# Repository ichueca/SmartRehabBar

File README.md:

# SmartRehabBar

**SmartRehabBar** es un proyecto centrado en el **desarrollo de un sistema inteligente que se integra en barras de rehabilitación**, permitiendo medir de forma objetiva la fuerza de apoyo ejercida por pacientes durante ejercicios de recuperación funcional.

El sistema utiliza **células de carga** para registrar la carga aplicada, enviando los datos en tiempo real a una plataforma web para su visualización. Esto permite a los profesionales sanitarios realizar un seguimiento cuantitativo de la evolución del paciente.

Además, el proyecto está diseñado con un enfoque **educativo y modular**, facilitando su uso en Formación Profesional y permitiendo futuras ampliaciones como análisis avanzado e integración de inteligencia artificial.

---

## 🎯 Objetivos del proyecto

* Medir de forma objetiva la **fuerza de apoyo** durante ejercicios de rehabilitación.
* Registrar el **tiempo de carga** y detectar descompensaciones.
* Facilitar datos cuantitativos al fisioterapeuta.
* Desarrollar un sistema **replicable, modular y de bajo coste**.
* Servir como base para futuras ampliaciones (doble apoyo, IA, análisis avanzado).

---

## 🧩 Arquitectura general del sistema

El sistema electrónico se compone de los siguientes bloques:

1. Sensórica de fuerza mediante células de carga.
2. Amplificación y conversión ADC con HX711.
3. Microcontrolador ESP32 para procesado y comunicaciones.
4. Sistema de alimentación autónomo con batería Li-Ion.
5. Comunicación WiFi con servidor remoto para visualización de datos.

---

## 🧪 Material electrónico utilizado

### Sensores

* **Células de carga resistivas** (galgas extensométricas).
* Configuración en puente de Wheatstone para mayor estabilidad.

### Conversión y amplificación

* **HX711**

  * ADC de 24 bits específico para células de carga.
  * Alta precisión para señales de baja variación.

### Microcontrolador

* **ESP32 / ESP32-C3 SuperMini**

  * Lectura del HX711.
  * Procesado de datos.
  * Comunicación WiFi.
  * Envío de datos a backend REST.

### Alimentación

* **Batería Li-Ion 18650** (3.0–4.2 V).
* **MCP73871**

  * Gestión de carga.
  * Power-path (uso y carga simultánea).
* **Convertidor Buck-Boost (TPS63020)**

  * Generación de tensión estable para el sistema (3.3 V).
* **Divisor resistivo**

  * Medición del voltaje de batería mediante ADC.

---

## 🧠 Firmware

En este repositorio se incluyen varias versiones del firmware:

### 🔹 PesajeV1

Primera versión funcional del sistema.

**Características:**

* Medición de fuerza en **un único punto de apoyo**.
* Lectura mediante HX711.
* Envío de datos de peso.
* No incluye medición de batería.
* Base para validación inicial.

---

### 🔹 PesajeV2

Versión mejorada del sistema.

**Novedades:**

* ✅ Medición de **nivel de batería en porcentaje**.
* ✅ Lectura de batería mediante ADC + divisor resistivo.
* ✅ Calibración del ADC para mayor precisión.
* ✅ Mejora en estabilidad de lectura.

---

### 🔹 PesajeV3

Versión actual del sistema.

**Novedades principales:**

* ✅ Medición de **doble apoyo (pie izquierdo y derecho)**.
* ✅ Uso de **dos módulos HX711** (uno por cada plataforma).
* ✅ Migración a **ESP32-C3 SuperMini** (reducción de tamaño y consumo).
* ✅ Lectura simultánea de ambos sensores.
* ✅ Envío independiente de datos de cada pie al backend.
* ✅ Mejora en la arquitectura del firmware (estructura modular).

Esta versión permite analizar **asimetrías de carga entre ambos pies**, siendo mucho más útil en entornos reales de rehabilitación.

---

### 🔮 Versiones futuras

* Mejora de filtrado y tratamiento de señal.
* Detección de eventos (apoyo, descarga, equilibrio).
* Optimización de consumo energético.
* Integración de análisis avanzado e IA.
* Visualización avanzada de métricas (balance, evolución, tendencias).

---

## 🔌 Hardware (KiCad)

El repositorio incluye el diseño electrónico completo desarrollado en **KiCad**:

### Contenido:

* 📄 Esquema eléctrico
* 🧩 Diseño de PCB
* 📦 Archivos listos para fabricación

### Versiones:

* Hardware compatible con **PesajeV1**
* Hardware actualizado para **PesajeV2 (medición de batería)**
* 🆕 Hardware **SmartRehab V3**

  * Soporte para **doble HX711**
  * Integración con **ESP32-C3 SuperMini**
  * Optimización del sistema de alimentación
  * Diseño compacto orientado a integración en plataforma

---

## 🔁 Pasos para la replicación

1. Definición del caso de uso.
2. Selección de sensores de fuerza.
3. Integración con HX711.
4. Implementación con ESP32.
5. Diseño del sistema de alimentación.
6. Desarrollo del firmware.
7. Validación con cargas reales.

---

## ⚠️ Consideraciones importantes

* Este sistema es una **herramienta de apoyo**, no un dispositivo médico certificado.
* La fijación mecánica de las células de carga es crítica.
* El sistema está diseñado para ser **modular y ampliable**.
* La medición de batería requiere calibración del ADC.
* Las mediciones de peso requieren **calibración (tara + escala)** tras cambios mecánicos.

---

## 📁 Estructura del repositorio

* `/firmware`

  * `PesajeV1`
  * `PesajeV2`
  * `PesajeV3` 🆕
* `/hardware`

  * `PCB_SmartRehab_V1`
  * `PCB_SmartRehab_V2`
  * `PCB_SmartRehab_V3` 🆕
* `/docs` → Documentación adicional

---

## 📱 Repositorio de la App

Frontend y visualización de datos:
https://github.com/ichueca/SmartRehabBar-App

---

## 👥 Autores

* Jonathan Arizala – https://lasalleberrozpe.eus
* Ainhoa Domínguez – https://nazaret.eus/
* Iñigo Chueca – https://www.zabalburu.org

Proyecto subvencionado por la Viceconsejería de Formación Profesional del Gobierno Vasco a través de https://tknika.eus/

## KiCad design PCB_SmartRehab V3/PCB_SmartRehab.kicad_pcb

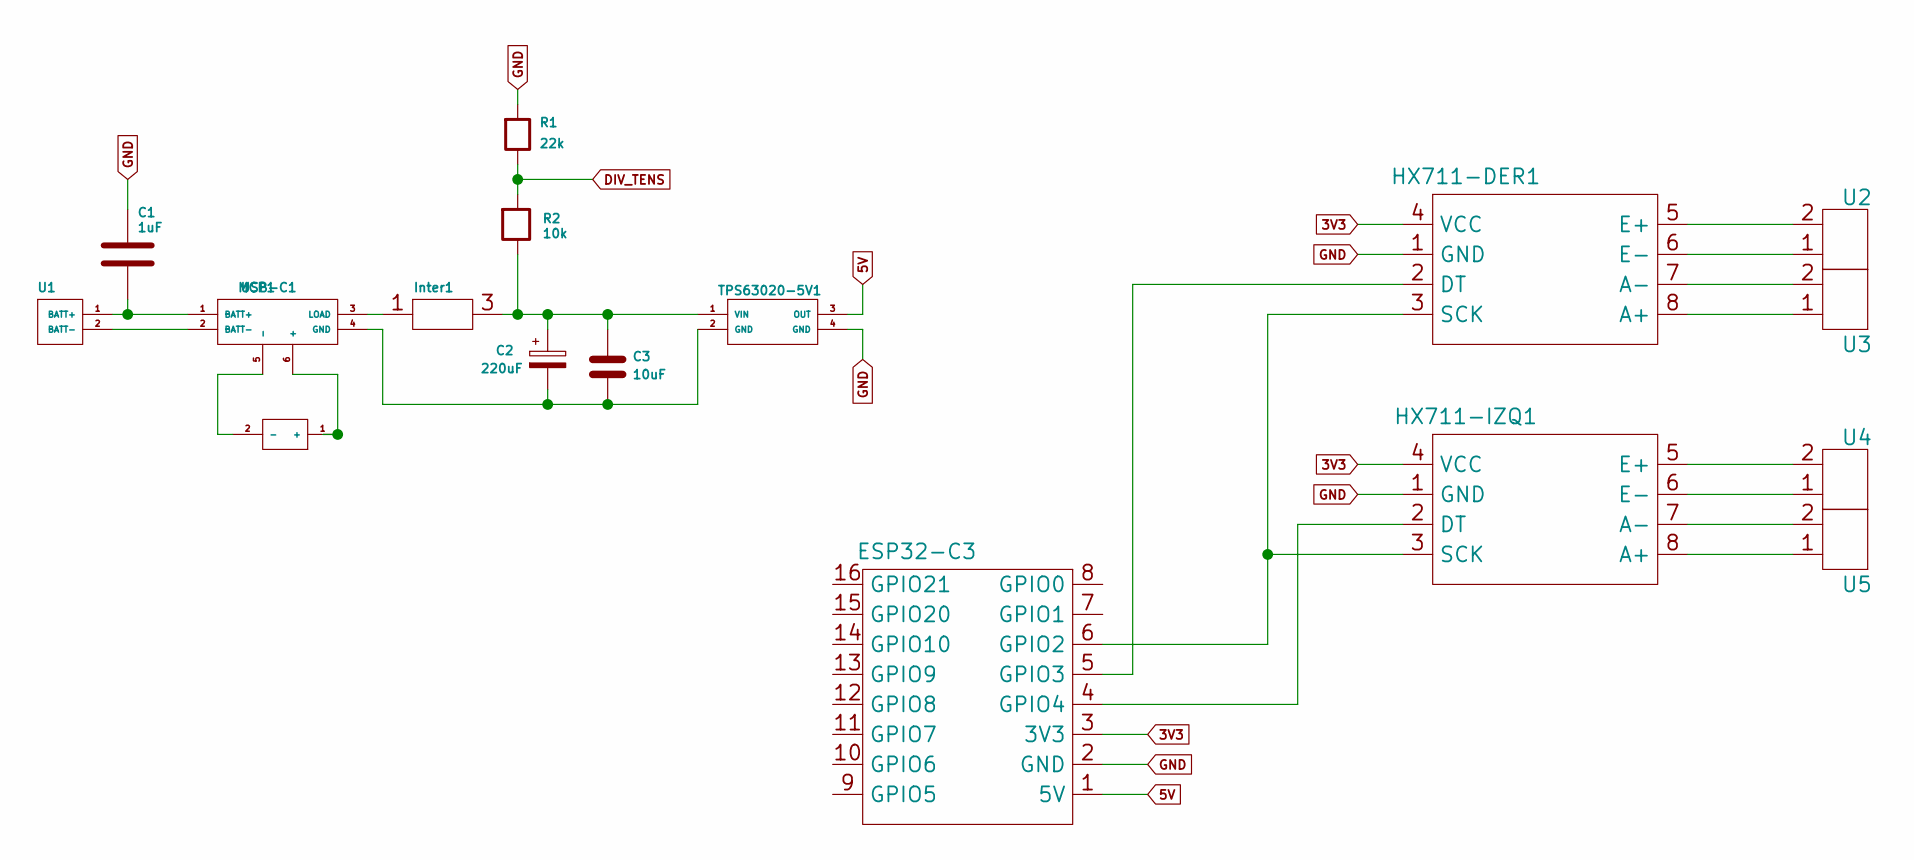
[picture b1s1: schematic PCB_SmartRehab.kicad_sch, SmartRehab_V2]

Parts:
C1: 1uF; C_Rect_L7.0mm_W6.0mm_P5.00mm
C2: 220uF; CP_Radial_D8.0mm_P3.50mm
C3: 10uF; C_Radial_D5.0mm_H11.0mm_P2.00mm
ESP32-C3: ESP32-C3 Supermini
HX711-DER1, HX711-IZQ1: HX711
Inter1: Interruptor3Pines
MCP1: MCP73871
R1: 22k; R_Axial_DIN0207_L6.3mm_D2.5mm_P10.16mm_Horizontal
R2: 10k; R_Axial_DIN0207_L6.3mm_D2.5mm_P10.16mm_Horizontal
TPS63020-5V1: TPS63020
U1, U2, U3, U4, U5: Conn5mm_02x01
USB-C1: USB-C

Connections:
3V3: ESP32-C3.3 (3V3), HX711-DER1.4 (VCC), HX711-IZQ1.4 (VCC)
5V: ESP32-C3.1 (5V), TPS63020-5V1.3 (OUT)
DIV_TENS: R1.2, R2.1
unnamed: ESP32-C3.6 (GPIO2), HX711-DER1.3 (SCK), HX711-IZQ1.3 (SCK)
unnamed: ESP32-C3.5 (GPIO3), HX711-DER1.2 (DT)
unnamed: ESP32-C3.4 (GPIO4), HX711-IZQ1.2 (DT)
unnamed: HX711-DER1.8 (A+), U3.1
unnamed: HX711-DER1.7 (A-), U3.2
unnamed: HX711-DER1.5 (E+), U2.2
unnamed: HX711-DER1.6 (E-), U2.1
unnamed: HX711-IZQ1.8 (A+), U5.1
unnamed: HX711-IZQ1.7 (A-), U5.2
unnamed: HX711-IZQ1.5 (E+), U4.2
unnamed: HX711-IZQ1.6 (E-), U4.1
unnamed: MCP1.6 (+), USB-C1.1 (+)
unnamed: MCP1.5 (-), USB-C1.2 (-)
unnamed: C1.2, MCP1.1 (BATT+), U1.1 (BATT+)
unnamed: MCP1.2 (BATT-), U1.2 (BATT-)
unnamed: Inter1.1, MCP1.3 (LOAD)
unnamed: C2.1, C3.1, Inter1.3, R2.2, TPS63020-5V1.1 (VIN)

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
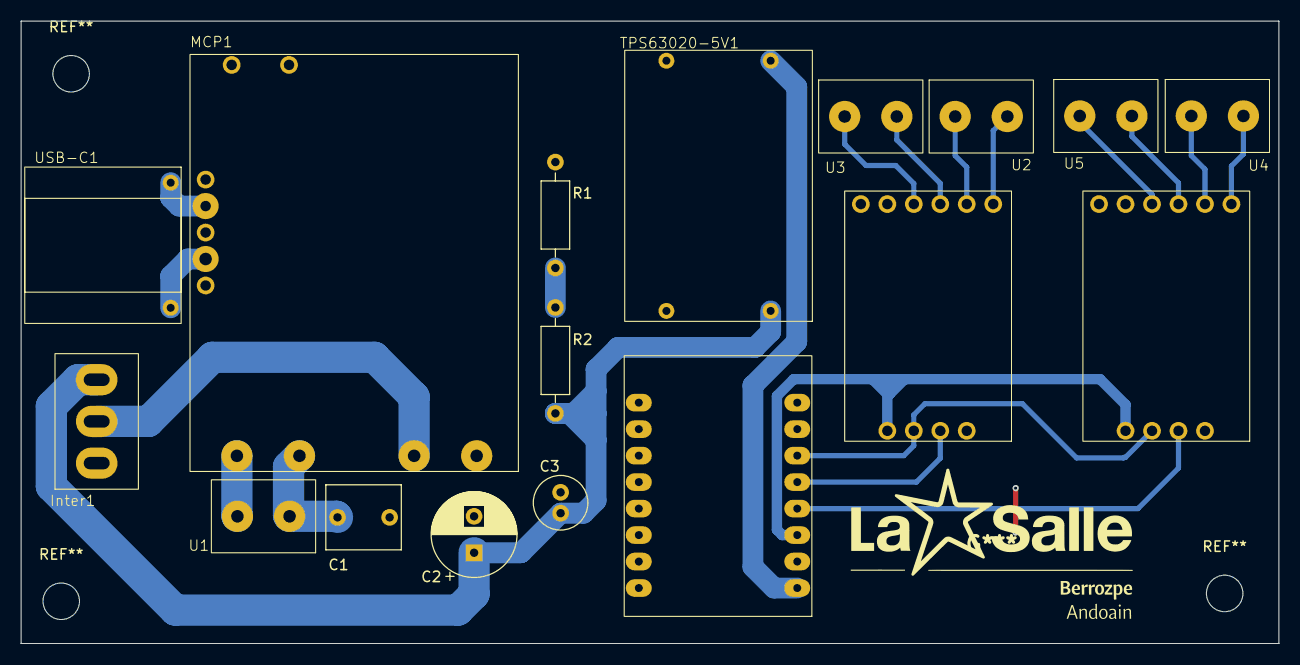
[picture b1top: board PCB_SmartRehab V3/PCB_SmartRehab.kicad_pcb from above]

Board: 2 copper layers, 120.7 x 59.7 mm, 17 parts (0 on the bottom side), 21 nets.

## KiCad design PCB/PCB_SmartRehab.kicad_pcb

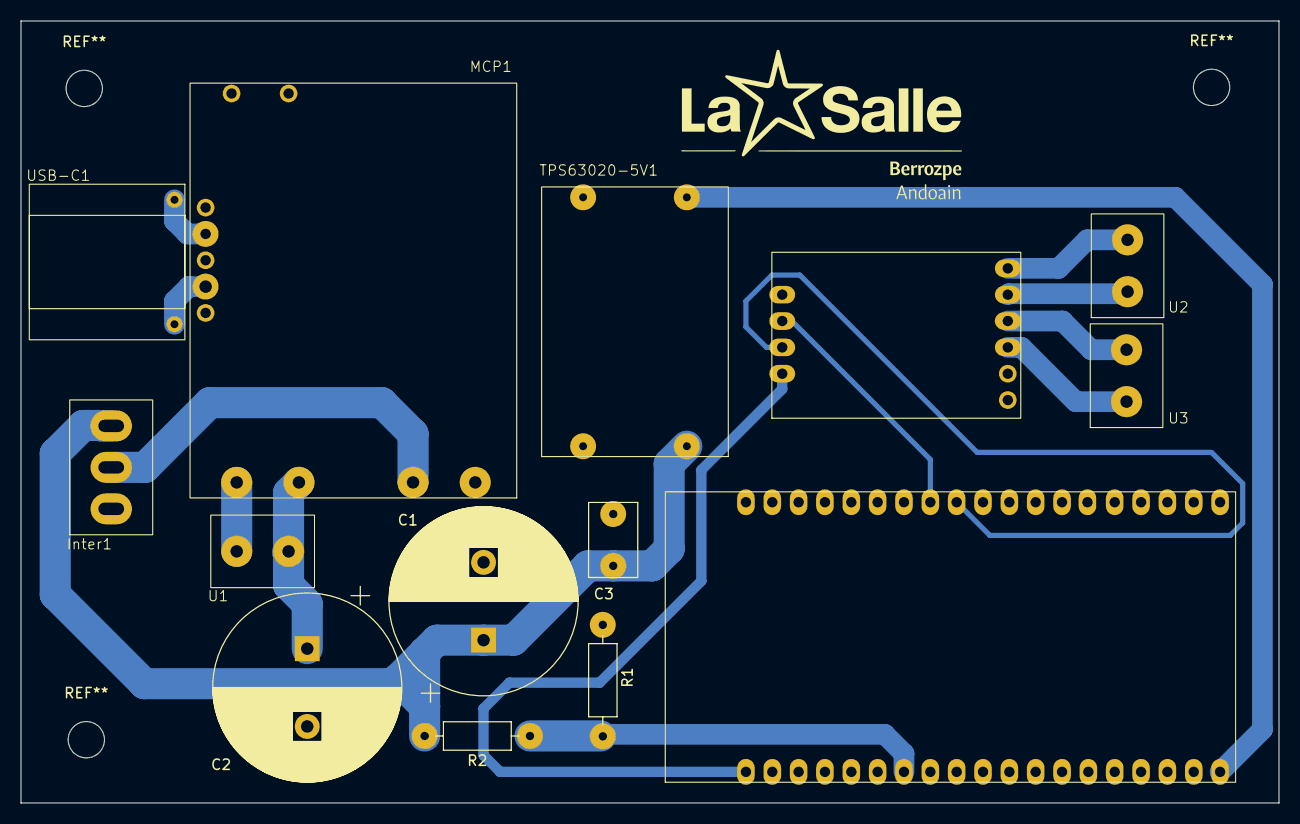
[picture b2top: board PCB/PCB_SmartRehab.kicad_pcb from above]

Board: 2 copper layers, 121.3 x 75.4 mm, 14 parts (0 on the bottom side), 16 nets.

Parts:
C1: 4700uF; CP_Radial_D18.0mm_P7.50mm
C2: 1uF; CP_Radial_D18.0mm_P7.50mm
C3: 10uF; C_Rect_L7.0mm_W4.5mm_P5.00mm
ESP32: ESP32
HX711: HX711
Inter1: Interruptor3Pines
MCP1: MCP73871
R1: 10k; R_Axial_DIN0207_L6.3mm_D2.5mm_P10.16mm_Horizontal
R2: 22k; R_Axial_DIN0207_L6.3mm_D2.5mm_P10.16mm_Horizontal
TPS63020-5V1: TPS63020
U1, U2, U3: Conn5mm_02x01
USB-C1: USB-C

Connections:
5V: ESP32.50 (5V), TPS63020-5V1.3 (OUT)
DIV_TENS: ESP32.32 (GPIO32), R1.2, R2.1
GND: C1.2, C2.2, ESP32.40 (GND), HX711.1 (GND), MCP1.4 (GND), R1.1, TPS63020-5V1.2 (GND), TPS63020-5V1.4 (GND)
unnamed: ESP32.55 (3V3), HX711.4 (VCC)
unnamed: ESP32.18 (GPIO18), HX711.3 (SCK)
unnamed: ESP32.19 (GPIO19), HX711.2 (DT)
unnamed: HX711.8 (A+), U3.1
unnamed: HX711.7 (A-), U3.2
unnamed: HX711.5 (E+), U2.2
unnamed: HX711.6 (E-), U2.1
unnamed: MCP1.6 (+), USB-C1.1 (+)
unnamed: MCP1.5 (-), USB-C1.2 (-)
unnamed: C2.1, MCP1.1 (BATT+), U1.1 (BATT+)
unnamed: MCP1.2 (BATT-), U1.2 (BATT-)
unnamed: Inter1.1, MCP1.3 (LOAD)
unnamed: C1.1, C3.1, Inter1.3, R2.2, TPS63020-5V1.1 (VIN)

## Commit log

2025-11-07 Inicio Proyecto
2025-12-18 Subida la primera version del programa. Monitorización de 1 balanza en pantalla
2025-12-18 Actualizado Readme.md
2026-03-24 Actualiza README y añade nuevos archivos del proyecto
    Actualiza README y añade nuevos archivos del proyecto
2026-05-08 Añadida version V3. Ver Readme.
